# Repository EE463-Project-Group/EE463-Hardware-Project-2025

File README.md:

# EE 463 Hardware Project

## DC Motor Drive

**Partners:** 
- Kaan Demirkoparan
- Metin Özdemir
- Ali Tarık Birsoy

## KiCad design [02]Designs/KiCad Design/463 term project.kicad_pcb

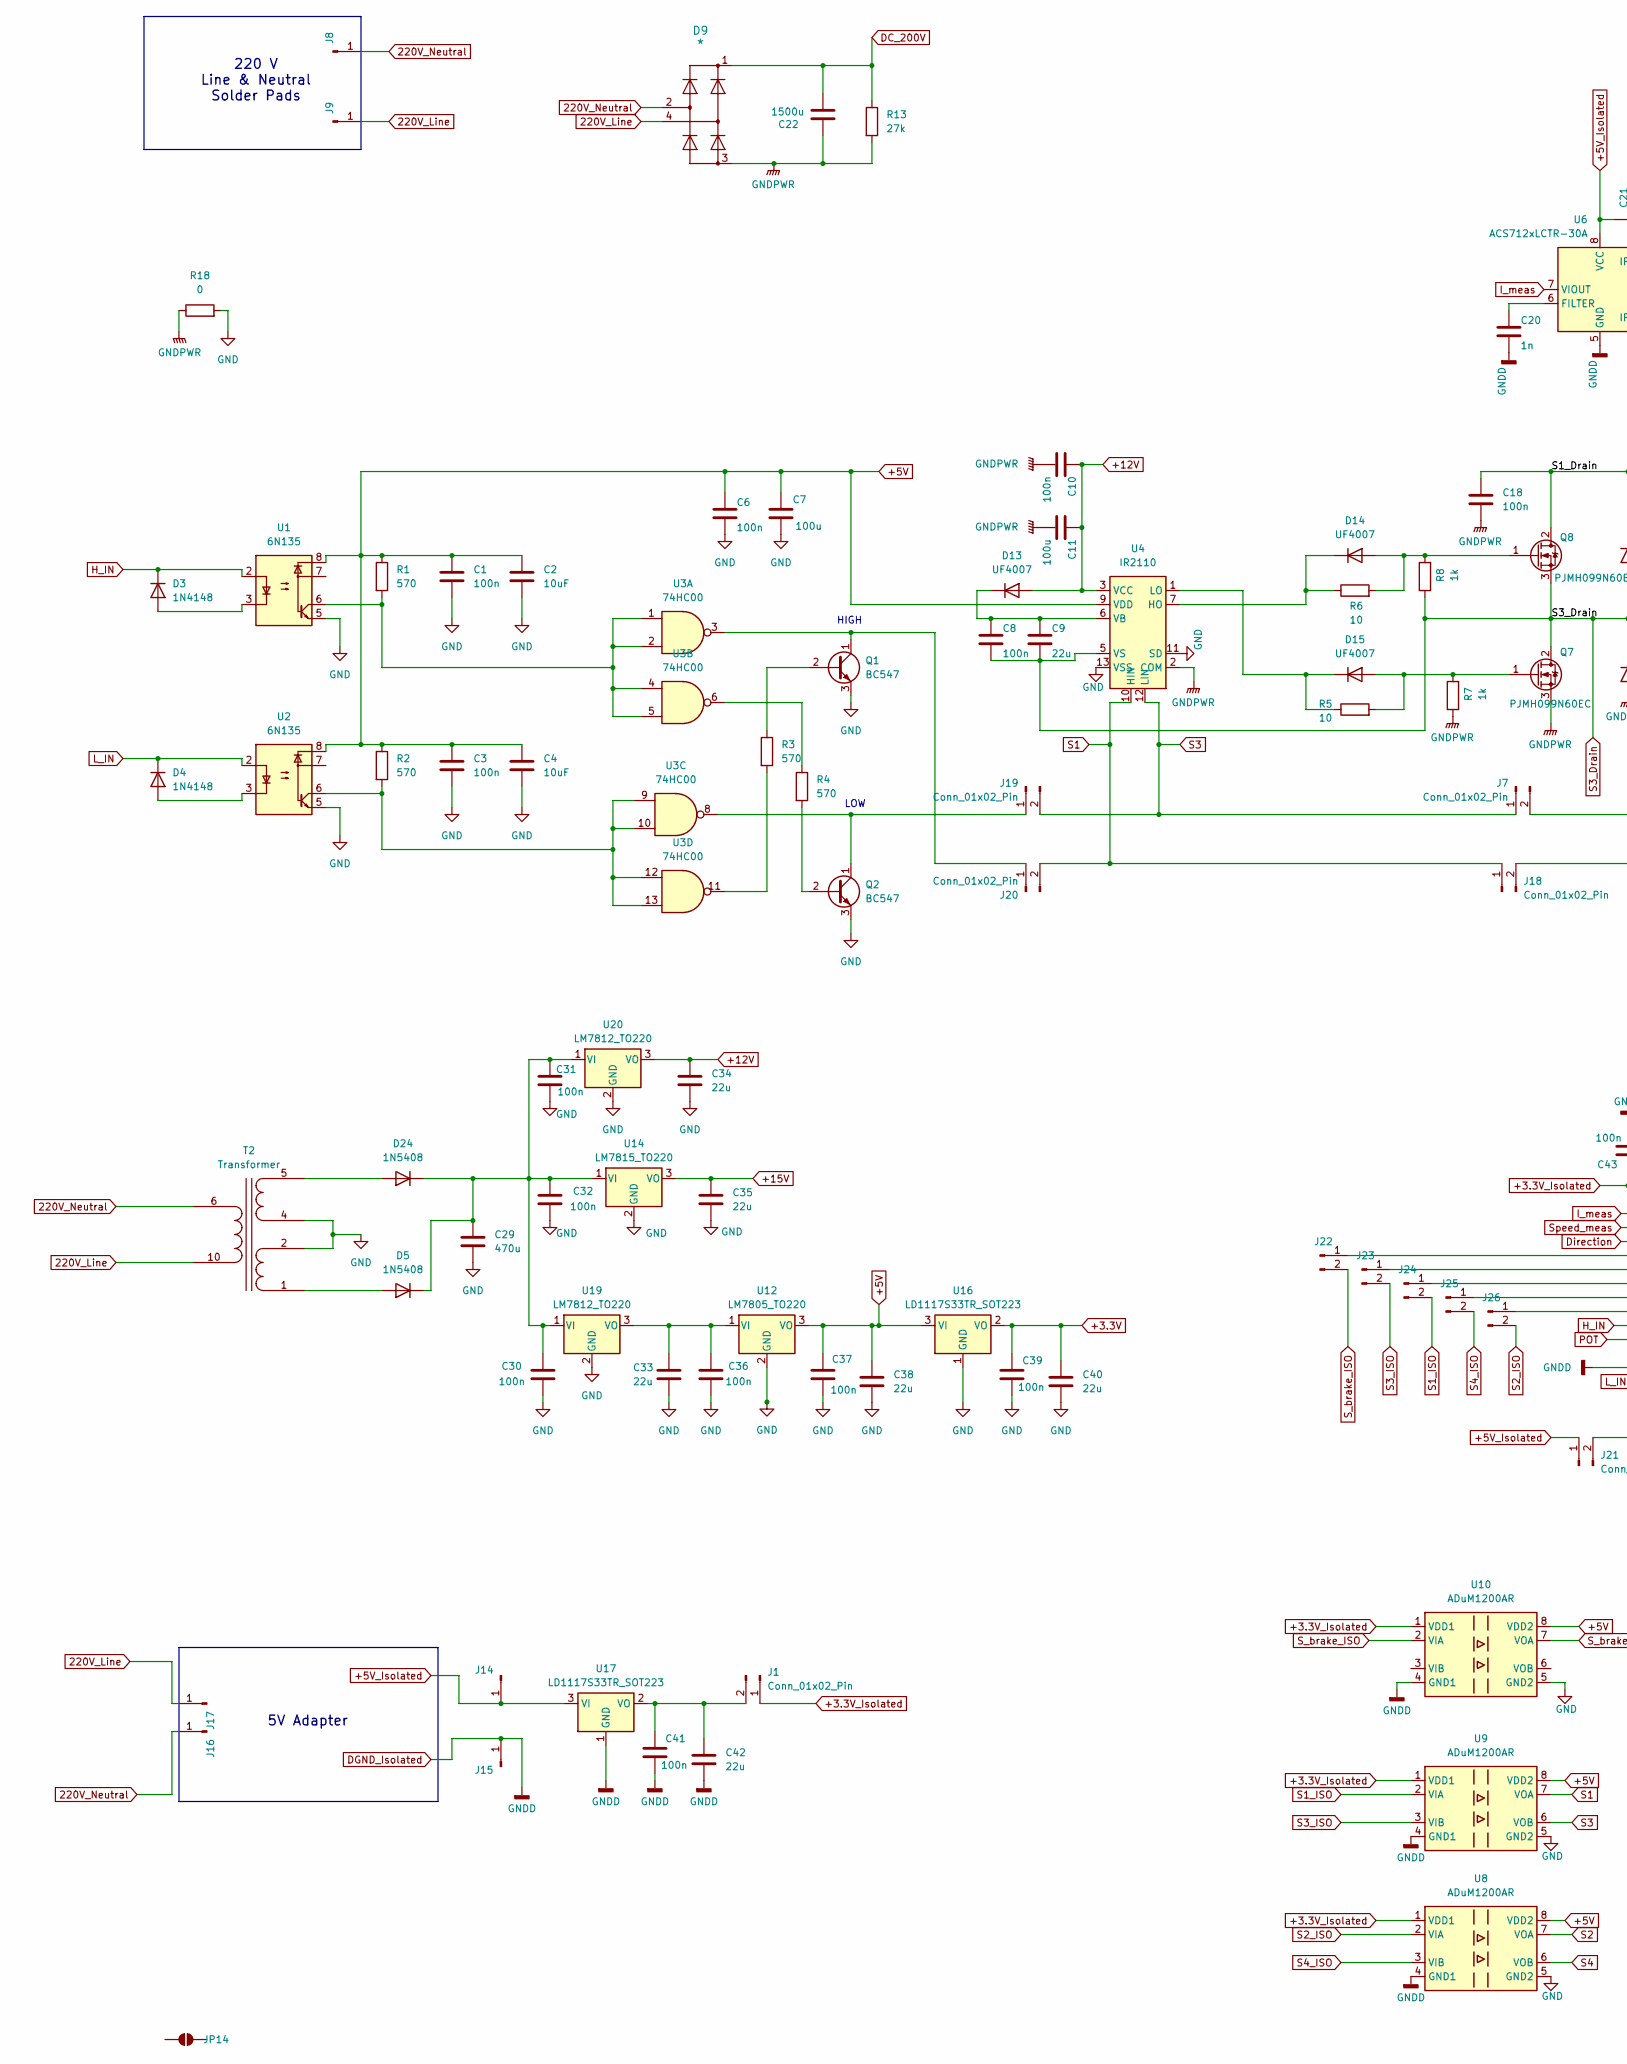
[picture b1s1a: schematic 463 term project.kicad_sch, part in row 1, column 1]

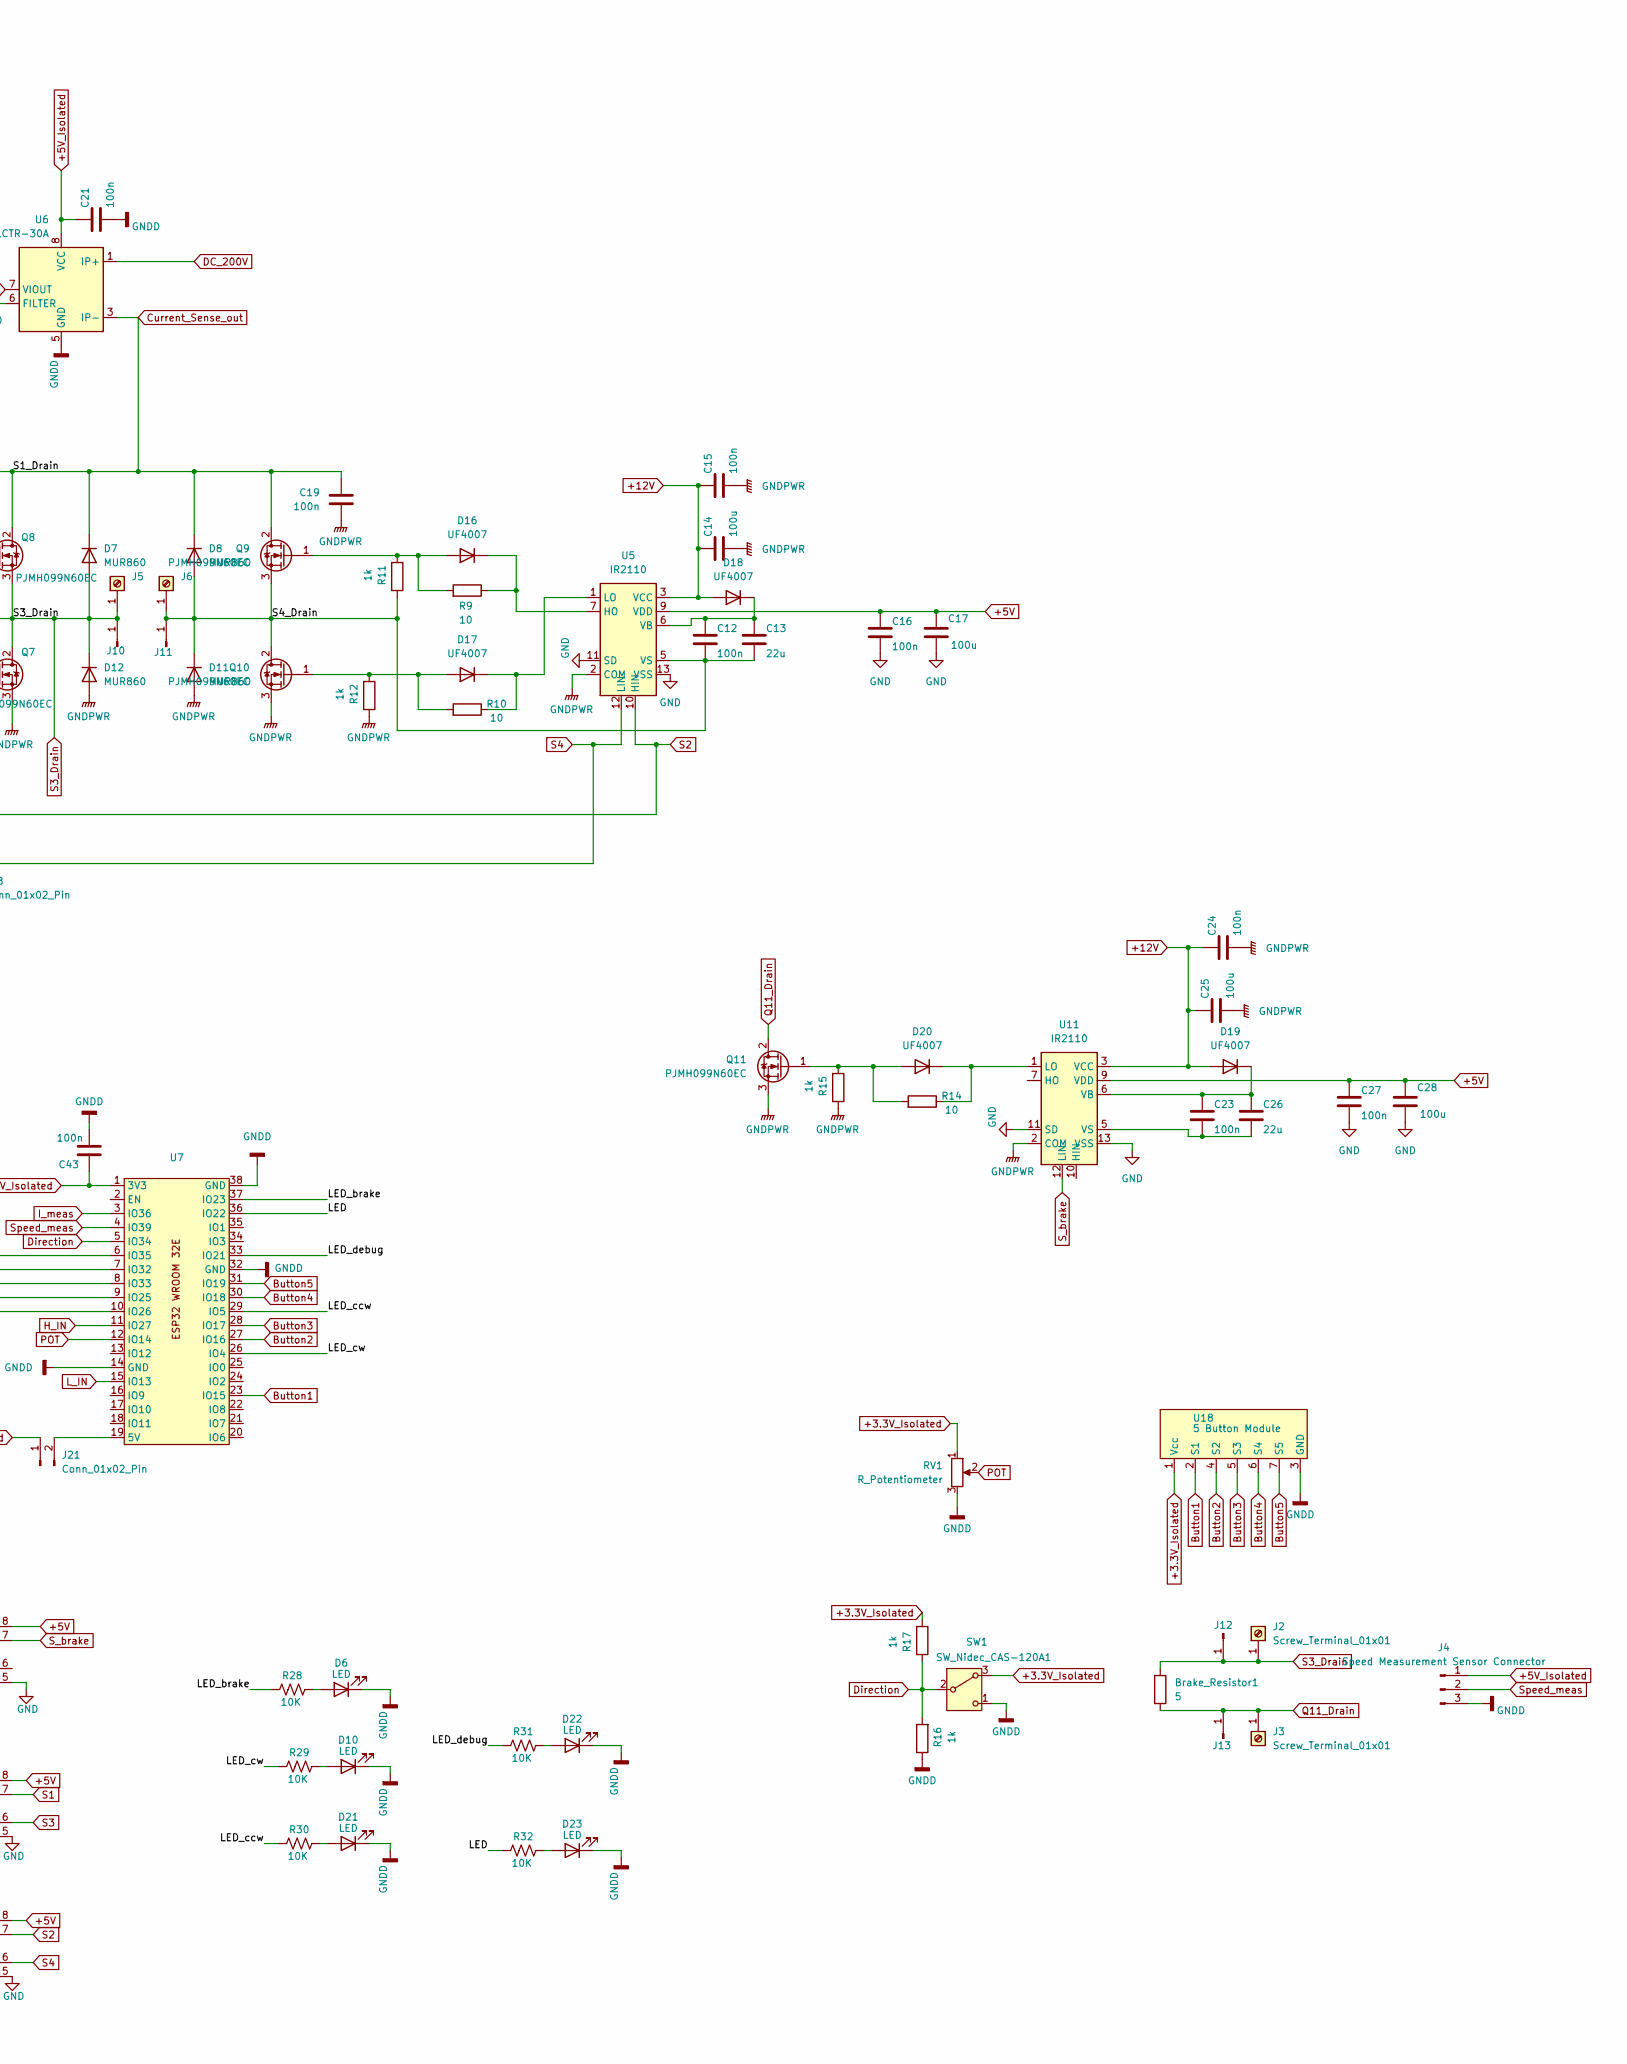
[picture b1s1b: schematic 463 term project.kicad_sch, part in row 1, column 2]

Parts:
Brake_Resistor1: 5
C1, C3, C6, C8, C10, C12, C15, C16, C18, C19, C23, C24, C27, C30, C31, C32, C36, C37, C39, C41, C43: 100n; C_Disc_D5.0mm_W2.5mm_P5.00mm
C2, C4: 10uF; CP_Radial_D6.3mm_P2.50mm
C7, C11, C14, C17, C25, C28: 100u; CP_Radial_D8.0mm_P5.00mm
C9, C13, C26, C33, C34, C35, C38, C40, C42: 22u; CP_Radial_D8.0mm_P5.00mm
C20: 1n; 0603 Large
C21: 100n; 0603 Large
C22: 1500u; 1500uF
C29: 470u; CP_Radial_D10.0mm_P2.50mm
D3, D4: 1N4148; D_DO-35_SOD27_P7.62mm_Horizontal
D5, D24: 1N5408; D_DO-201AD_P15.24mm_Horizontal
D6, D10, D21, D22, D23: LED; 0603 Medium
D7, D8, D11, D12: MUR860; TO-220-2_Vertical
D9: *; KBPC3510FP
D13, D14, D15, D16, D17, D18, D19, D20: UF4007; D_DO-41_SOD81_P10.16mm_Horizontal
J1, J7, J18, J19, J20, J21, J22, J23, J24, J25, J26: Conn_01x02_Pin; PinHeader_1x02_P2.54mm_Vertical
J2, J3, J5, J6: Screw_Terminal_01x01; Untitled
J4: Speed Measurement Sensor Connector; PinHeader_1x03_P2.54mm_Vertical
J8, J9, J10, J11, J12, J13, J16, J17: Conn_01x01_Pin; SolderWirePad_1x01_SMD_5x10mm
J14, J15: Conn_01x01_Pin; SolderWirePad_1x01_SMD_1x2mm
JP14: SolderJumper_2_Open; SolderJumper-2_P1.3mm_Open_TrianglePad1.0x1.5mm
Q1, Q2: BC547; TO-92_Inline
Q7, Q8, Q9, Q10, Q11: PJMH099N60EC; TO-247-3_Vertical
R1, R2, R3, R4: 570; R_Axial_DIN0207_L6.3mm_D2.5mm_P10.16mm_Horizontal
R5, R6, R9, R10, R14: 10; R_Axial_DIN0207_L6.3mm_D2.5mm_P10.16mm_Horizontal
R7, R8, R11, R12, R15, R16, R17: 1k; R_Axial_DIN0207_L6.3mm_D2.5mm_P10.16mm_Horizontal
R13: 27k; R_Axial_DIN0207_L6.3mm_D2.5mm_P10.16mm_Horizontal
R18: 0; R_Axial_DIN0207_L6.3mm_D2.5mm_P10.16mm_Horizontal
R28, R29, R30, R31, R32: 10K; 0603 Medium
RV1: R_Potentiometer; PinHeader_1x03_P2.54mm_Vertical
SW1: SW_Nidec_CAS-120A1; PinHeader_1x03_P2.54mm_Vertical
T2: Transformer; Transformer_Breve_TEZ-35x42
U1, U2: 6N135; DIP-8_W7.62mm
U3: 74HC00; DIP-14_W7.62mm_Socket
U4, U5, U11: IR2110; DIP-14_W7.62mm
U6: ACS712xLCTR-30A; SOIC-8_3.9x4.9mm_P1.27mm
U7: ESP32_WROOM_32X
U8, U9, U10: ADuM1200AR; SOIC-8_3.9x4.9mm_P1.27mm
U12: LM7805_TO220; TO-220-3_Vertical
U14: LM7815_TO220; TO-220-3_Vertical
U16, U17: LD1117S33TR_SOT223; TO-220-3_Vertical
U18: 5 Button Module; 5 button module
U19, U20: LM7812_TO220; TO-220-3_Vertical

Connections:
220V_Line: D9.4 (Input_~), J9.1, J17.1, T2.10 (AB)
220V_Neutral: D9.2 (Input_~), J8.1, J16.1, T2.6 (AA)
+3.3V: C39.1, C40.1, U16.2 (VO)
+3.3V_Isolated: C43.1, J1.1, R17.1, RV1.1, SW1.3 (A), U7.1 (3V3), U8.1 (VDD1), U9.1 (VDD1), U10.1 (VDD1), U18.1 (Vcc)
+5V: C1.1, C2.1, C3.1, C4.1, C6.1, C7.1, C16.1, C17.1, C27.1, C28.1, C37.1, C38.1, R1.1, R2.1, U1.8, U2.8, U4.9 (VDD), U5.9 (VDD), U8.8 (VDD2), U9.8 (VDD2), U10.8 (VDD2), U11.9 (VDD), U12.3 (VO), U16.3 (VI)
+5V_Isolated: C21.1, J4.1, J14.1, J21.1, U6.8 (VCC), U17.3 (VI)
+12V: C10.1, C11.1, C14.1, C15.1, C24.1, C25.1, C34.1, D13.2 (A), D18.2 (A), D19.2 (A), U4.3 (VCC), U5.3 (VCC), U11.3 (VCC), U20.3 (VO)
+15V: C35.1, U14.3 (VO)
/LED: R32.1, U7.36 (IO22)
/LED_brake: R28.1, U7.37 (IO23)
/LED_ccw: R30.1, U7.29 (IO5)
/LED_cw: R29.1, U7.26 (IO4)
/LED_debug: R31.1, U7.33 (IO21)
/S4_Drain: C12.2, C13.2, D8.2 (A), D11.1 (K), J6.1, J11.1, Q9.3 (S), Q10.2 (D), R11.1, U5.5 (VS)
Button1: U7.23 (IO15), U18.2 (S1)
Button2: U7.27 (IO16), U18.4 (S2)
Button3: U7.28 (IO17), U18.5 (S3)
Button4: U7.30 (IO18), U18.6 (S4)
Button5: U7.31 (IO19), U18.7 (S5)
Current_Sense_out: C18.1, C19.1, D7.1 (K), D8.1 (K), Q8.2 (D), Q9.2 (D), U6.3 (IP-), U6.4 (IP-)
DC_200V: C22.2, D9.1 (+), R13.1, U6.1 (IP+), U6.2 (IP+)
DGND_Isolated: C20.2, C21.2, C41.2, C42.2, C43.2, D6.1 (K), D10.1 (K), D21.1 (K), D22.1 (K), D23.1 (K), J4.3, J15.1, R16.1, RV1.3, SW1.1 (C), U6.5 (GND), U7.14 (GND), U7.32 (GND), U7.38 (GND), U8.4 (GND1), U9.4 (GND1), U10.4 (GND1), U17.1 (GND), U18.3 (GND)
Direction: R16.2, R17.2, SW1.2 (B), U7.5 (IO34)
GND: C1.2, C2.2, C3.2, C4.2, C6.2, C7.2, C16.2, C17.2, C27.2, C28.2, C29.2, C30.2, C31.2, C32.2, C33.2, C34.2, C35.2, C36.2, C37.2, C38.2, C39.2, C40.2, Q1.3 (E), Q2.3 (E), R18.2, T2.2 (SC), T2.4 (SB), U1.5, U2.5, U4.11 (SD), U4.13 (VSS), U5.11 (SD), U5.13 (VSS), U8.5 (GND2), U9.5 (GND2), U10.5 (GND2), U11.11 (SD), U11.13 (VSS), U12.2 (GND), U14.2 (GND), U16.1 (GND), U19.2 (GND), U20.2 (GND)
GNDPWR: C10.2, C11.2, C14.2, C15.2, C18.2, C19.2, C22.1, C24.2, C25.2, D9.3 (-), D11.2 (A), D12.2 (A), Q7.3 (S), Q10.3 (S), Q11.3 (S), R7.1, R12.1, R13.2, R15.1, R18.1, U4.2 (COM), U5.2 (COM), U11.2 (COM)
H_IN: D3.1 (K), U1.2, U7.11 (IO27)
I_meas: U6.7 (VIOUT), U7.3 (IO36)
L_IN: D4.1 (K), U2.2, U7.15 (IO13)
unnamed: D3.2 (A), U1.3
unnamed: D4.2 (A), U2.3
unnamed: D5.2 (A), T2.1 (SD)
unnamed: D6.2 (A), R28.2
unnamed: D10.2 (A), R29.2
unnamed: C8.1, C9.1, D13.1 (K), U4.6 (VB)
unnamed: D14.2 (A), Q8.1 (G), R6.2, R8.2
unnamed: D14.1 (K), R6.1, U4.7 (HO)
unnamed: D15.2 (A), Q7.1 (G), R5.2, R7.2
unnamed: D15.1 (K), R5.1, U4.1 (LO)
unnamed: D16.2 (A), Q9.1 (G), R9.2, R11.2
unnamed: D16.1 (K), R9.1, U5.7 (HO)
unnamed: D17.2 (A), Q10.1 (G), R10.2, R12.2
unnamed: D17.1 (K), R10.1, U5.1 (LO)
unnamed: C12.1, C13.1, D18.1 (K), U5.6 (VB)
unnamed: C23.1, C26.1, D19.1 (K), U11.6 (VB)
unnamed: D20.2 (A), Q11.1 (G), R14.2, R15.2
unnamed: D20.1 (K), R14.1, U11.1 (LO)
unnamed: D21.2 (A), R30.2
unnamed: D22.2 (A), R31.2
unnamed: D23.2 (A), R32.2
unnamed: D24.2 (A), T2.5 (SA)
unnamed: C29.1, C30.1, C31.1, C32.1, D5.1 (K), D24.1 (K), U14.1 (VI), U19.1 (VI), U20.1 (VI)
unnamed: C41.1, C42.1, J1.2, U17.2 (VO)
unnamed: J19.1, Q2.1 (C), U3.8
unnamed: J20.1, Q1.1 (C), U3.3
unnamed: J21.2, U7.19 (5V)
unnamed: J22.1, U7.6 (IO35)
unnamed: J23.1, U7.7 (IO32)
unnamed: J24.1, U7.8 (IO33)
unnamed: J25.1, U7.9 (IO25)
unnamed: J26.1, U7.10 (IO26)
unnamed: Q1.2 (B), R3.1
unnamed: Q2.2 (B), R4.2
unnamed: R1.2, U1.6, U3.1, U3.2, U3.4, U3.5
unnamed: R2.2, U2.6, U3.9, U3.10, U3.12, U3.13
unnamed: R3.2, U3.11
unnamed: R4.1, U3.6
unnamed: C20.1, U6.6 (FILTER)
unnamed: C23.2, C26.2, U11.5 (VS)
unnamed: C33.1, C36.1, U12.1 (VI), U19.3 (VO)
POT: RV1.2, U7.12 (IO14)
Q11_Drain: Brake_Resistor1.2, J3.1, J13.1, Q11.2 (D)
S1: J18.1, J20.2, U4.10 (HIN), U9.7 (VOA)
S1_ISO: J24.2, U9.2 (VIA)
S2: J7.2, U5.10 (HIN), U8.7 (VOA)
S2_ISO: J26.2, U8.2 (VIA)
S3: J7.1, J19.2, U4.12 (LIN), U9.6 (VOB)
S3_Drain: Brake_Resistor1.1, C8.2, C9.2, D7.2 (A), D12.1 (K), J2.1, J5.1, J10.1, J12.1, Q7.2 (D), Q8.3 (S), R8.1, U4.5 (VS)
S3_ISO: J23.2, U9.3 (VIB)
S4: J18.2, U5.12 (LIN), U8.6 (VOB)
S4_ISO: J25.2, U8.3 (VIB)
S_brake: U10.7 (VOA), U11.12 (LIN)
S_brake_ISO: J22.2, U10.2 (VIA)
Speed_meas: J4.2, U7.4 (IO39)

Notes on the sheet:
220 V Line & Neutral Solder Pads
HIGH
LOW
5V Adapter

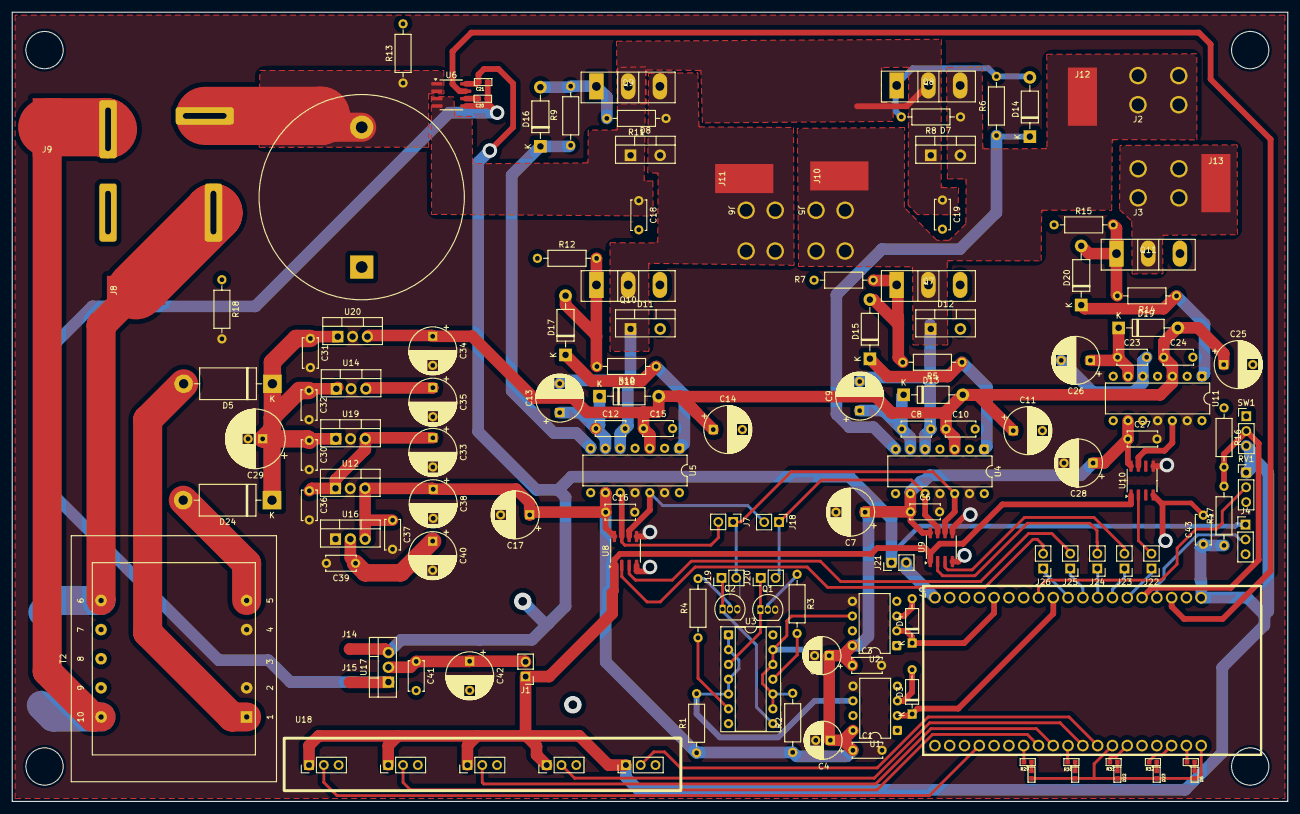
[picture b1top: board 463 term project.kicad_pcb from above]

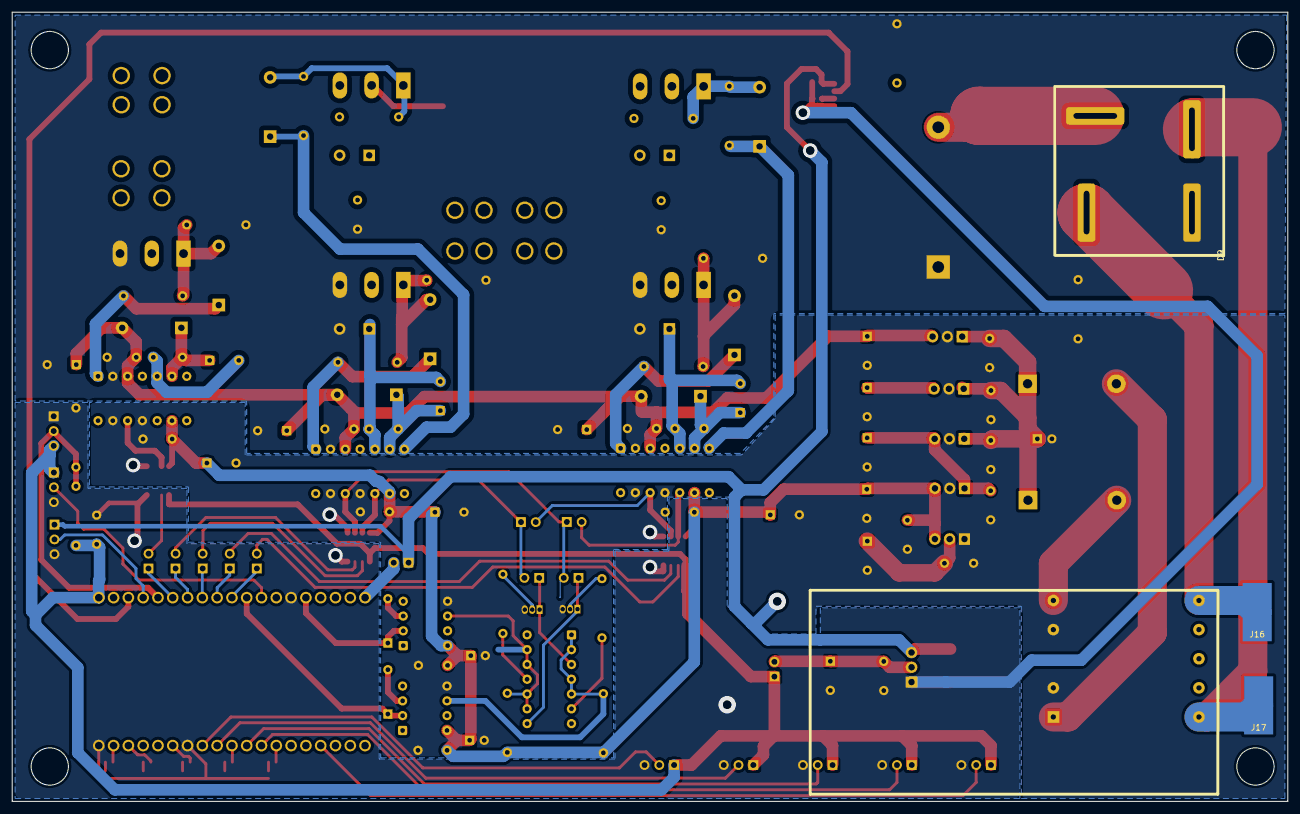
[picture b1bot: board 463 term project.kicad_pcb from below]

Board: 2 copper layers, 219.0 x 135.5 mm, 141 parts (3 on the bottom side), 83 nets.

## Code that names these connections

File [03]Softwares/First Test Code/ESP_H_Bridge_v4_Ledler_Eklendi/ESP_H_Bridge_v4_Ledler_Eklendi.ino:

// ESP32 WROOM-32E Hibrit Motor Kontrol (Serial + Buton)
// -----------------------------------------------------
// ÖNCELİK SIRASI:
// 1. Fiziksel Fren Butonu (Basılı Tutulduğu Sürece)
// 2. Serial Komutlar (Anlık Tepki)
// 3. Diğer Butonlar (Seç -> Başlat Mantığı)

// --- PIN TANIMLAMALARI ---
// Motor Pinleri
#define U1HIN 33  // PWM Q1
#define U2HIN 26  // PWM Q3
#define U1LIN 32  // LOW Q2
#define U2LIN 25  // LOW Q4

#define POT 14    // Hız Ayarı

// Buton Pinleri
#define BTN_ILERI 15
#define BTN_GERI  16
#define BTN_START 17
#define BTN_STOP  18
#define BTN_FREN  19

// Gösterge LED'leri
#define LED_CW      4   // İleri Yön Seçim LEDi
#define LED_CCW     5   // Geri Yön Seçim LEDi

// Yeni Şematik Düzeni:
#define LED_ALIVE   21  // "Disable/Boşta" LEDi - Motor Boşta iken yanar
#define LED_DEBUG   22  // "Sistem Alive" - Motor İleri/Geri dönerken yanar
#define LED_BRAKE   23  // Fren LEDi - Sadece Fren anında yanar

// --- AYARLAR ---
const int MAX_PWM = 230; // %90 Duty Cycle (Bootstrap Koruması)

// --- DEĞİŞKENLER ---
char calismaModu = 'b'; // 'b'=Boşta, 'i'=İleri, 'g'=Geri, 'f'=Fren
char secilenYon = 'i';  // 'i'=İleri, 'g'=Geri (Varsayılan İleri)
bool frenBasiliMi = false;

// Serial Zamanlayıcı
unsigned long sonYazdirmaZamani = 0;
const int yazdirmaAraligi = 200; 

void setup() {
  Serial.begin(115200);
  Serial.println("--- HIBRIT MOTOR KONTROL SISTEMI ---");
  Serial.println("Kontrol: Butonlar (Active HIGH) VEYA Serial Monitor");
  Serial.println("Serial Komutlar: 'i'(Ileri), 'g'(Geri), 'b'/'d'(Dur/Bosta), 'f'(Fren)");
  
  // Güvenli Başlangıç (Pinleri önce LOW yap)
  digitalWrite(U1HIN, LOW); digitalWrite(U2HIN, LOW);
  digitalWrite(U1LIN, LOW); digitalWrite(U2LIN, LOW);
  
  pinMode(U1HIN, OUTPUT); pinMode(U2HIN, OUTPUT);
  pinMode(U1LIN, OUTPUT); pinMode(U2LIN, OUTPUT);
  
  pinMode(LED_CW, OUTPUT);
  pinMode(LED_CCW, OUTPUT);
  pinMode(LED_BRAKE, OUTPUT);
  pinMode(LED_ALIVE, OUTPUT); 
  pinMode(LED_DEBUG, OUTPUT); 

  // BUTON AYARLARI (Active HIGH için PULLDOWN kullanıyoruz)
  // Not: Butona basılmadığında 0V (LOW) olması için bu gereklidir.
  // Butonun bir ucu IO pinine, diğer ucu 3.3V'a bağlı olmalı.
  pinMode(BTN_ILERI, INPUT_PULLDOWN);
  pinMode(BTN_GERI,  INPUT_PULLDOWN);
  pinMode(BTN_START, INPUT_PULLDOWN);
  pinMode(BTN_STOP,  INPUT_PULLDOWN);
  pinMode(BTN_FREN,  INPUT_PULLDOWN);

  bostaBirak();
  ledleriGuncelle();
}

void loop() {
  // ---------------------------------------------------------
  // 1. EN YÜKSEK ÖNCELİK: FİZİKSEL FREN BUTONU (Active HIGH)
  // ---------------------------------------------------------
  if (digitalRead(BTN_FREN) == HIGH) { // Basılınca HIGH veriyor
    if (calismaModu != 'f') {
      frenYap();
      calismaModu = 'f';
      frenBasiliMi = true;
    }
    motorSurucusuGuncelle(); // Freni uygula
    
    // DÜZELTME 2: Fren basılıyken de serial verisinin akmaya devam etmesi sağlandı.
    // 'return' etmeden önce yazdırma kontrolü yapıyoruz.
    if (millis() - sonYazdirmaZamani > yazdirmaAraligi) {
      bilgiYazdir();
      sonYazdirmaZamani = millis();
    }
    
    delay(10); 
    return; // Fren basılıyken başka komut dinleme!
  } 
  else {
    // Fren butonu bırakıldı mı?
    if (frenBasiliMi == true) {
      bostaBirak();
      calismaModu = 'b';
      frenBasiliMi = false;
    }
  }

  // ---------------------------------------------------------
  // 2. SERIAL HABERLEŞME KONTROLÜ
  // ---------------------------------------------------------
  if (Serial.available() > 0) {
    char gelenVeri = Serial.read();
    
    // Geçerli komut kontrolü
    if (gelenVeri == 'i' || gelenVeri == 'g' || gelenVeri == 'f' || 
        gelenVeri == 'b' || gelenVeri == 'd') { 
      
      if (gelenVeri == 'd') gelenVeri = 'b';

      // Yön değişimi varsa ölü zaman (Deadtime) uygula
      if (calismaModu != gelenVeri && calismaModu != 'b') {
        bostaBirak();
        delay(100); 
      }

      calismaModu = gelenVeri;
      
      if (gelenVeri == 'i') secilenYon = 'i';
      if (gelenVeri == 'g') secilenYon = 'g';
      
      ledleriGuncelle(); 
      
      Serial.print("SERIAL KOMUT: "); 
      Serial.println(gelenVeri);
    }
  }

  // ---------------------------------------------------------
  // 3. BUTON KONTROLLERİ (Active HIGH)
  // ---------------------------------------------------------
  
  // STOP Butonu
  if (digitalRead(BTN_STOP) == HIGH) {
    if (calismaModu != 'b') {
      bostaBirak();
      calismaModu = 'b';
      Serial.println("BUTON: STOP");
      delay(200); 
    }
  }

  // DÜZELTME 1: Yön Seçim Butonlarına Serial çıktısı ve debounce eklendi.
  if (digitalRead(BTN_ILERI) == HIGH) {
    secilenYon = 'i';
    ledleriGuncelle();
    Serial.println("BUTON: YON SECIMI -> ILERI");
    delay(200); // Bas-çek kararlılığı için
  }
  if (digitalRead(BTN_GERI) == HIGH) {
    secilenYon = 'g';
    ledleriGuncelle();
    Serial.println("BUTON: YON SECIMI -> GERI");
    delay(200); // Bas-çek kararlılığı için
  }

  // START Butonu
  if (digitalRead(BTN_START) == HIGH) {
    if (calismaModu != secilenYon) {
      if (calismaModu != 'b') {
        bostaBirak();
        delay(100);
      }
      calismaModu = secilenYon;
      Serial.println("BUTON: START");
      delay(200); 
    }
  }

  // ---------------------------------------------------------
  // 4. MOTOR SÜRÜŞ VE EKRAN
  // ---------------------------------------------------------
  motorSurucusuGuncelle();

  if (millis() - sonYazdirmaZamani > yazdirmaAraligi) {
    bilgiYazdir();
    sonYazdirmaZamani = millis();
  }
}

// --- YARDIMCI FONKSİYONLAR ---

void motorSurucusuGuncelle() {
  int potDegeri = analogRead(POT);
  int pwmHiz = map(potDegeri, 0, 4095, 0, MAX_PWM);
  
  switch (calismaModu) {
    case 'i': ileriSur(pwmHiz); break;
    case 'g': geriSur(pwmHiz); break;
    case 'f': frenYap(); break;     
    case 'b': default: bostaBirak(); break;
  }
  
  ledleriGuncelle();
}

void ledleriGuncelle() {
  // 1. YÖN SEÇİM LEDLERİ
  if (secilenYon == 'i') {
    digitalWrite(LED_CW, HIGH);
    digitalWrite(LED_CCW, LOW);
  } else {
    digitalWrite(LED_CW, LOW);
    digitalWrite(LED_CCW, HIGH);
  }
  
  // 2. FREN LEDİ
  digitalWrite(LED_BRAKE, (calismaModu == 'f') ? HIGH : LOW);

  // 3. ALIVE LED (Motor dönüyorsa)
  if (calismaModu == 'i' || calismaModu == 'g') {
    digitalWrite(LED_ALIVE, HIGH);
  } else {
    digitalWrite(LED_ALIVE, LOW);
  }

  // 4. DEBUG LED (Motor boşta ise)
  if (calismaModu == 'b') {
    digitalWrite(LED_DEBUG, HIGH);
  } else {
    digitalWrite(LED_DEBUG, LOW);
  }
}

void ileriSur(int hiz) {
  digitalWrite(U1LIN, LOW);
  digitalWrite(U2HIN, LOW);
  digitalWrite(U2LIN, HIGH); 
  analogWrite(U1HIN, hiz);   
}

void geriSur(int hiz) {
  digitalWrite(U1HIN, LOW);
  digitalWrite(U2LIN, LOW);
  digitalWrite(U1LIN, HIGH);
  analogWrite(U2HIN, hiz);
}

void frenYap() {
  analogWrite(U1HIN, 0); 
  analogWrite(U2HIN, 0);
  digitalWrite(U1LIN, HIGH); 
  digitalWrite(U2LIN, HIGH);
}

void bostaBirak() {
  analogWrite(U1HIN, 0);
  analogWrite(U2HIN, 0);
  digitalWrite(U1LIN, LOW);
  digitalWrite(U2LIN, LOW);
}

void bilgiYazdir() {
  String durumStr;
  if (calismaModu == 'i') durumStr = "ILERI SURUS";
  else if (calismaModu == 'g') durumStr = "GERI SURUS";
  else if (calismaModu == 'f') durumStr = "!!! FREN !!!";
  else durumStr = "BOSTA (STOP)";

  String secimStr = (secilenYon == 'i') ? "ILERI" : "GERI";
  int pot = analogRead(POT);
  int hizYuzde = map(pot, 0, 4095, 0, 90);

  Serial.printf("MOD: %-13s | SECIM: %-5s | HIZ: %%%d \n", 
                durumStr.c_str(), secimStr.c_str(), hizYuzde);
}

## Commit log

2025-11-03 Update project title and add partner names
2025-11-19 [01] Created Folders & Researched Project Links Added
2025-11-19 Added New Folders
2025-11-24 [Researches] Add various research links for motor controllers
2025-11-24 Rename 'Researchs' to 'Researches' in file path
    Renamed the file '[01]Researchs/Links.md' to '[01]Researches/Links.md' to correct the folder name spelling.
2025-11-25 [Researches] Update Links.md with new resources and corrections
    Added new links for brushed DC servo drive and updated MC-2100 Motor Controller section.
2025-11-25 fully discrete buck design
    buck design report which I did during my internship, might prove useful
2025-12-01 Add HV Floating MOS-Gate Driver ICs section
    Added a section for HV Floating MOS-Gate Driver ICs with a relevant link.
2025-12-01 simple dc motor starter design
    without PI controller
2025-12-03 [Researches] Update Links.md with new resources
    Added new resources for IR2110 Gate Driver and Motor Speed Control.
2025-12-03 Add commit message formatting instructions
2025-12-03 [Researches] Update Links.md with new resources
    Added additional YouTube links for motor speed and current control.
2025-12-03 [Researches] Component List Mosfet and Gate Driver Added
    Added detailed specifications and models for Mosfet and Gate Driver components.
2025-12-03 [Researches] Updated component list
    Added a reference link for Qg specification at 20KHz switching frequency.
2025-12-04 Rectifier design
2025-12-04 Designs: Low Voltage Generation
    5,12,15, 3.3v generated. Note: need to download necessary models to ltspice
2025-12-04 Researches: Application notes for TL431
2025-12-05 version 3 is completed for feedback session
2025-12-05 [Reports] Add Simulation Report document
    Added the initial version of the Simulation Report in the reports directory.
2025-12-05 Simulations: auxiliary power stage
2025-12-05 Designs: Auxiliary power stage
2025-12-05 [Reports] Finalized Preliminary Design Report
2025-12-05 [Reports] Added Preliminary Design Presentation
    Added the Preliminary Design Presentation document to the reports directory for project documentation.
2025-12-06 Add new file 'a' in KiCad Designs directory
2025-12-06 Schematic Design of Motor Controller
2025-12-07 Component list
2025-12-07 [Docs] Added BOM list
    Added BOM List.xlsx to the Docs folder. Renamed preliminary design presentation and report files from [05]Reports to [06]Reports for better organization. Added KiCad schematic lock file.
2025-12-17 [Simulations] Added Braking To Simulations
2025-12-18 Schematic Updates: Added Brake Part
    auxlary power design added
2025-12-18 Schematic and Footprints are finished
2025-12-19 schematic is updated
2025-12-19 Layout.v1 finished & Schematic updates
2025-12-21 Layout and schematic updates
2025-12-21 [Design] Layout Finished
2025-12-22 [Design] Layout Finalized
2025-12-22 Updates on Layout and Schematic
2025-12-22 Updates on Layout
2025-12-24 Added Schematic PDF
2025-12-26 Reduced PCB Size
    This reverts commit fabae2b9b95dacba0e962aa67e5fb78db473a071.
2025-12-26 SVG Files
2025-12-30 Updated Simulation & Uploaded First Working ESP Code
2025-12-30 Minor PCB Shematic Correction & File Arrangements
2025-12-31 Software v2 Uploaded
2026-01-02 Schematic Update & New Software Update (LED and Buttons Added)
2026-01-06 Update Software. LEDs and Buttons Work
